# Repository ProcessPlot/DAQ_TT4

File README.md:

# DAQ_TT4
A simple, yet powerful data acquisition circuit that is basically an arduino compatible shield to read a 16-bit [ADC_MAX1300](https://datasheets.maximintegrated.com/en/ds/MAX1300-MAX1301.pdf) through the SPI interface. The board is enlarged to fit into an aluminum enclosure and use BNC input jacks.

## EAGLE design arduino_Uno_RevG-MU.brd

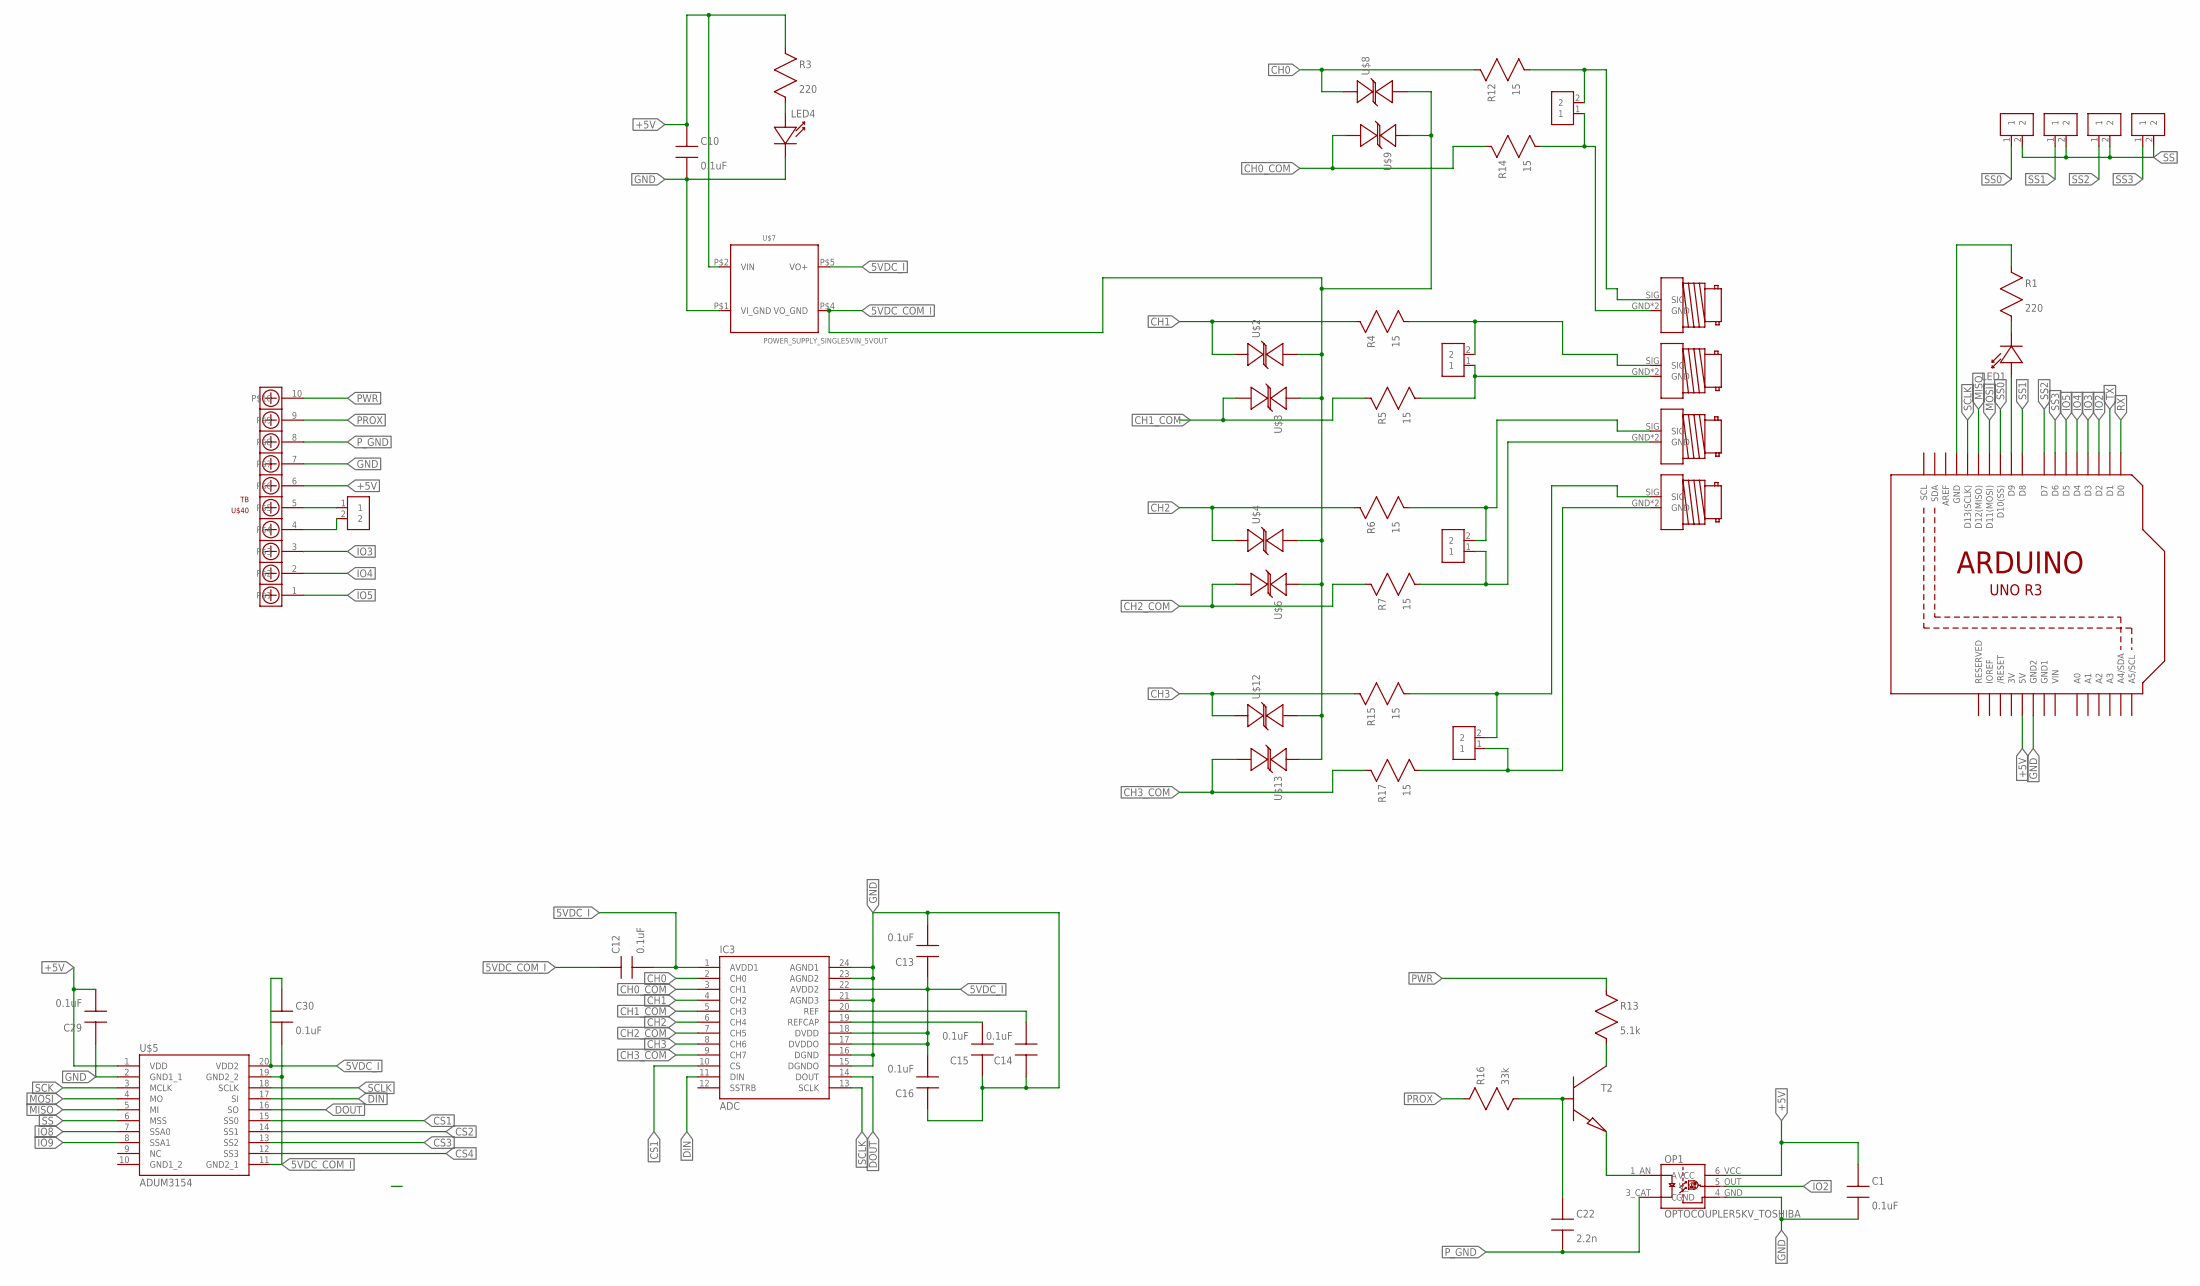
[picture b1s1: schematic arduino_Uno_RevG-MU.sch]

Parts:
C1, C10, C12, C13, C14, C15, C16, C29, C30: 0.1uF; 0805_SMD
C22: 2.2n; 0805_SMD
IC3: ADC; LS_ELECTRIC_HTSSOP24-PAD
LED1, LED4: LED0805_GREEN; LED_0805
OP1: OPTOCOUPLER5KV_TOSHIBA; SO6L
R1, R3: 220; 0805_SMD
R4, R5, R6, R7, R12, R14, R15, R17: 15; 0805_SMD
R13: 5.1k; 0805_SMD
R16: 33k; 0805_SMD
T2: TRANSISTOR_NPNMMBT3904L; SOT23
U4: ARDUINOR3-DIMENSION; ARDUINOR3
U$1: CH2; BNC
U$2, U$3, U$4, U$6, U$8, U$9, U$12, U$13: TSV14VAC_18VDC; 0805_SMD
U$5: ADUM3154; SSOP_20
U$7: POWER_SUPPLY_SINGLE5VIN_5VOUT; SMT-R1SE-0505
U$10, U$11, U$14, U$15, U$16, U$17, U$18, U$19, U$20: 1X2_HEADER1X2; 1X2_HEADER
U$34: CH1; BNC
U$35: CH3; BNC
U$36: CG4; BNC
U$40: TB; TB_10P

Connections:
3V: U4.3V
5VDC_COM_I: C12.1 (A), C30.2 (B), U$2.2 (GND), U$3.1 (+), U$4.2 (GND), U$5.11 (GND2_1), U$5.19 (GND2_2), U$6.1 (+), U$7.P$4 (VO_GND), U$8.2 (GND), U$9.1 (+), U$12.2 (GND), U$13.1 (+)
5VDC_I: C12.2 (B), C13.1 (A), C16.2 (B), C30.1 (A), IC3.1 (AVDD1), IC3.17 (DVDDO), IC3.18 (DVDD), IC3.22 (AVDD2), U$5.20 (VDD2), U$7.P$5 (VO+)
+5V: C1.1 (A), C10.1 (A), C29.2 (B), OP1.6_VCC (VCC), R3.1 (A), U4.5V, U$5.1 (VDD), U$7.P$2 (VIN), U$40.6
CH0: IC3.2 (CH0), R12.1 (A), U$8.1 (+)
CH0_COM: IC3.3 (CH1), R14.1 (A), U$9.2 (GND)
CH1: IC3.4 (CH2), R4.1 (A), U$2.1 (+)
CH1_COM: IC3.5 (CH3), R5.1 (A), U$3.2 (GND)
CH2: IC3.6 (CH4), R6.1 (A), U$4.1 (+)
CH2_COM: IC3.7 (CH5), R7.1 (A), U$6.2 (GND)
CH3: IC3.8 (CH6), R15.1 (A), U$12.1 (+)
CH3_COM: IC3.9 (CH7), R17.1 (A), U$13.2 (GND)
CS1: IC3.10 (CS), U$5.15 (SS0)
CS2: U$5.14 (SS1)
CS3: U$5.13 (SS2)
CS4: U$5.12 (SS3)
DIN: IC3.11 (DIN), U$5.17 (SI)
DOUT: IC3.14 (DOUT), U$5.16 (SO)
GND: C1.2 (B), C10.2 (B), C13.2 (B), C14.1 (A), C15.1 (A), C16.1 (A), C29.1 (A), IC3.15 (DGNDO), IC3.16 (DGND), IC3.21 (AGND3), IC3.23 (AGND2), IC3.24 (AGND1), LED4.C (-), OP1.4_GND (GND), R1.1 (A), U4.GND, U4.GND2, U$5.2 (GND1_1), U$7.P$1 (VI_GND), U$40.7
GND1: U4.GND1
IO2: OP1.5_OUT (V_O), U4.D2
IO3: U4.D3, U$40.3
IO4: U4.D4, U$40.2
IO5: U4.D5, U$40.1
IO8: U$5.7 (SSA0)
IO9: U$5.8 (SSA1)
MISO: U4.D12 (D12(MISO)), U$5.5 (MI)
MOSI: U4.D11 (D11(MOSI)), U$5.4 (MO)
unnamed: LED1.C (-), R1.2 (B)
unnamed: LED1.A (+), U4.D9
unnamed: U$20.2, U$40.4
unnamed: U$20.1, U$40.5
unnamed: LED4.A (+), R3.2 (B)
unnamed: C14.2 (B), IC3.20 (REF)
unnamed: C15.2 (B), IC3.19 (REFCAP)
unnamed: R4.2 (B), U$1.SIG, U$11.2
unnamed: R5.2 (B), U$1.GND, U$1.GND_INV (GND), U$11.1
unnamed: R15.2 (B), U$19.2, U$36.SIG
unnamed: R17.2 (B), U$19.1, U$36.GND, U$36.GND_INV (GND)
unnamed: OP1.1_AN (A), T2.2 (E)
unnamed: R13.2 (B), T2.3 (C)
unnamed: C22.1 (A), R16.2 (B), T2.1 (B)
unnamed: R12.2 (B), U$10.2, U$34.SIG
unnamed: R14.2 (B), U$10.1, U$34.GND, U$34.GND_INV (GND)
unnamed: R6.2 (B), U$18.2, U$35.SIG
unnamed: R7.2 (B), U$18.1, U$35.GND, U$35.GND_INV (GND)
PROX: R16.1 (A), U$40.9
PWR: R13.1 (A), U$40.10
P_GND: C22.2 (B), OP1.3_CAT (C), U$40.8
RX: U4.D0
SCK: U$5.3 (MCLK)
SCLK: IC3.13 (SCLK), U4.D13 (D13(SCLK)), U$5.18 (SCLK)
SS: U$5.6 (MSS), U$14.2, U$15.2, U$16.2, U$17.2
SS0: U4.D10 (D10(SS)), U$14.1
SS1: U4.D8, U$15.1
SS2: U4.D7, U$16.1
SS3: U4.D6, U$17.1
SSTRB: IC3.12 (SSTRB)
TX: U4.D1
VIN: U4.VIN

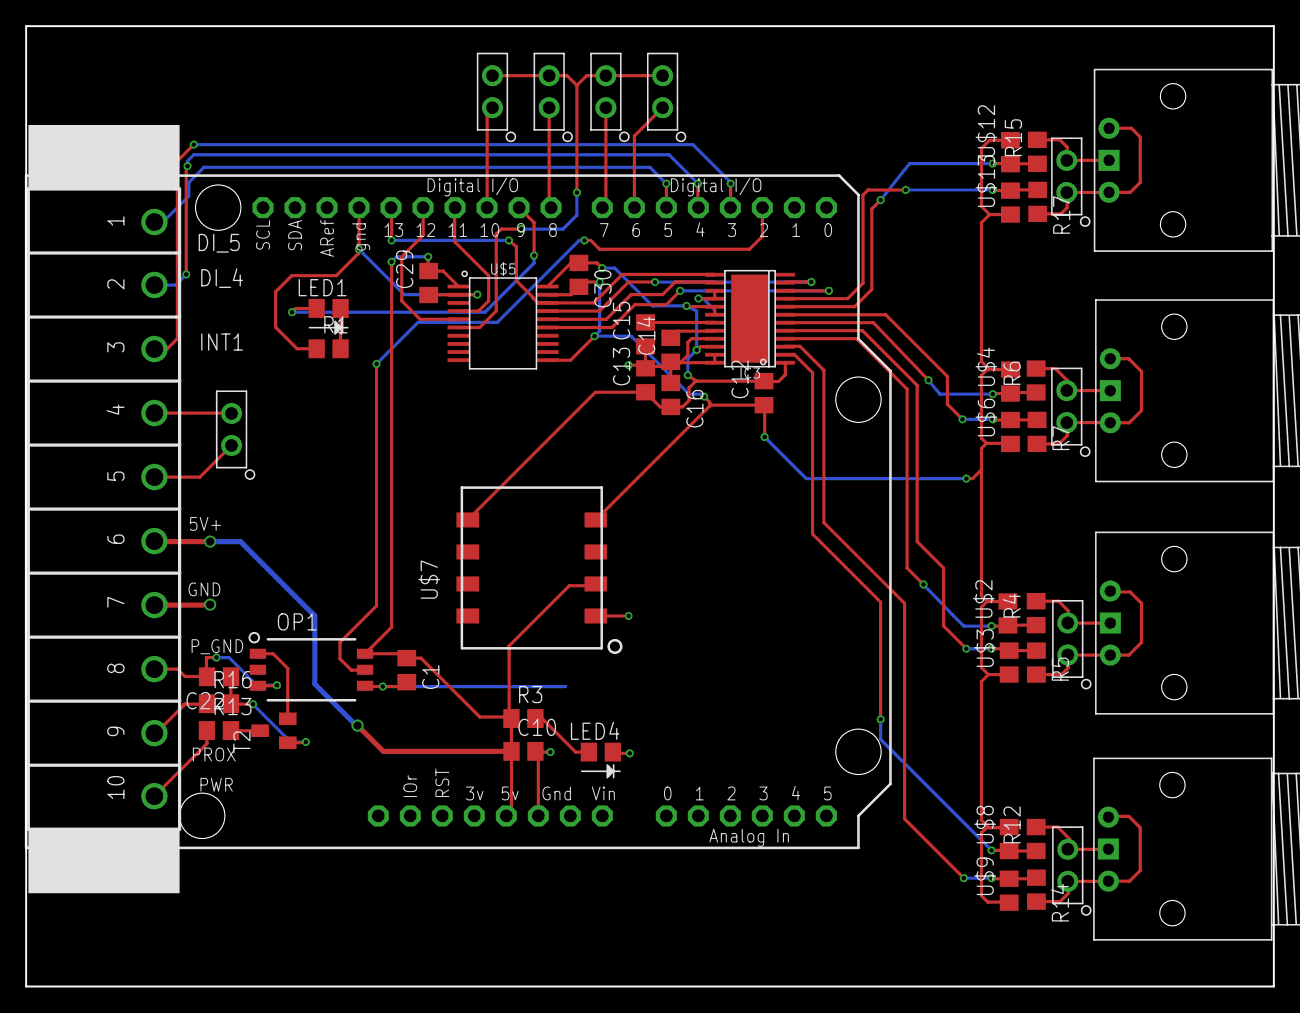
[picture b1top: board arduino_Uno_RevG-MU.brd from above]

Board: 2 copper layers, 99.0 x 76.2 mm, 52 parts (0 on the bottom side), 48 nets.

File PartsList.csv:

"Qty";"Value";"Device";"Package";"Parts";"Description";"DIGIKEY";"DIGIKEY_PLUG";"DIGIKEY_RECP";"MOUSER";"MPN";"MPN_PLUG";"MPN_RECP";
"2";"";"LED0805_GREEN";"LED_0805";"LED1, LED4";"LED - 574nm Diffused";"160-1423-1-ND";"";"";"";"LTST-C171GKT";"";"";
"1";"";"TRANSISTOR_NPNMMBT3904L";"SOT23";"T2";"Bipolar Transistor - BJT NPN GENERAL PURPOSE";"MMBT3904LT1GOSCT-ND";"";"";"";"MMBT3904LT1G";"";"";
"8";"";"TSV14VAC_18VDC";"0805_SMD";"U$2, U$3, U$4, U$6, U$8, U$9, U$12, U$13";"";"478-6867-1-ND";"";"";"";"VCAS08LC18A500DP";"";"";
"9";"0.1uF";"CAPACITOR0.1U_50V";"0805_SMD";"C1, C10, C12, C13, C14, C15, C16, C29, C30";"Capacitor (non polarity)";"399-1176-1-ND";"";"";"";"C0805C104M5UACTU";"";"";
"8";"15";"RESISTOR15_0805";"0805_SMD";"R4, R5, R6, R7, R12, R14, R15, R17";"Resistor 1MOhms";"311-15.0CRCT-ND";"";"";"";"RC0805FR-0715RL";"";"";
"8";"1X2_HEADER1X2";"1X2_HEADER1X2";"1X2_HEADER";"U$10, U$11, U$14, U$15, U$16, U$17, U$18, U$19";"";"WM4000-ND";"";"";"";"0022032021";"";"";
"1";"2.2n";"CAPACITOR2.2N_0805";"0805_SMD";"C22";"Capacitor (non polarity)";"399-1151-1-ND";"";"";"";"C0805C222K5RACTU";"";"";
"2";"220";"RESISTOR220_0805";"0805_SMD";"R1, R3";"Resistor 1MOhms";"311-220CRCT-ND";"";"";"";"RC0805FR-07220RL";"";"";
"1";"33k";"RESISTOR33K_0805";"0805_SMD";"R16";"Resistor 1MOhms";"311-33.0KCRCT-ND";"";"";"";"RC0805FR-0733KL";"";"";
"1";"5.1k";"RESISTOR5.1K_0805";"0805_SMD";"R13";"Resistor 1MOhms";"311-5.10KCRCT-ND";"";"";"";"RC0805FR-075K1L";"";"";
"1";"ADC";"ADC";"LS_ELECTRIC_HTSSOP24-PAD";"IC3";"4/8 Channel 16bit ADC with 4 wire SPI";"700-MAX1300AEUG+";"";"";"";"MAX1300AEUG+";"";"";
"1";"ADUM3154";"ADUM3154";"SSOP_20";"U$5";"";"ADUM3154ARSZ-RL7CT-ND";"";"";"";"ADUM3154ARSZ-RL7";"";"";
"1";"ARDUINOR3-DIMENSION";"ARDUINOR3-DIMENSION";"ARDUINOR3";"U4";"This is a new object for the new Arduino R3 - with extra pins that you may want to use (such as IOref, and duplicated A4/A5";"";"";"";"";"";"";"";
"1";"CG4";"BNC_INVBNC_INVERT";"BNC";"U$36";"";"";"";"";"523-31-5431-10RFX";"031-5431-10RFX";"";"";
"1";"CH1";"BNC_INVBNC_INVERT";"BNC";"U$34";"";"";"";"";"523-31-5431-10RFX";"031-5431-10RFX";"";"";
"1";"CH2";"BNC_INVBNC_INVERT";"BNC";"U$1";"";"";"";"";"523-31-5431-10RFX";"031-5431-10RFX";"";"";
"1";"CH3";"BNC_INVBNC_INVERT";"BNC";"U$35";"";"";"";"";"523-31-5431-10RFX";"031-5431-10RFX";"";"";
"1";"OPTOCOUPLER5KV_TOSHIBA";"OPTOCOUPLER5KV_TOSHIBA";"SO6L";"OP1";"High Speed Optocoupler 5MBd 1Ch 1.6mA";"TLP2745(TPECT-ND";"";"";"";"TLP2745(TP,E";"";"";
"1";"POWER_SUPPLY_SINGLE5VIN_5VOUT";"POWER_SUPPLY_SINGLE5VIN_5VOUT";"SMT-R1SE-0505";"U$7";"1kV/1W - 5Vin/5Vout";"945-1659-1-ND";"";"";"";"R1SE-0505-R";"";"";
"1";"TB";"TERMINAL_BLOCK_10PHOENIX_10";"TB_10P";"U$40";"";"";"277-5742-ND";"277-5950-ND";"";"";"1778069";"1776582";

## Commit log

2018-08-09 initial commit with README edit
2018-08-10 Initial eagle file
2018-08-10 updated gitignore to ignore backup files
2018-08-10 removed backup files
2018-08-15 First board order
2018-08-15 changed to 99mm board
